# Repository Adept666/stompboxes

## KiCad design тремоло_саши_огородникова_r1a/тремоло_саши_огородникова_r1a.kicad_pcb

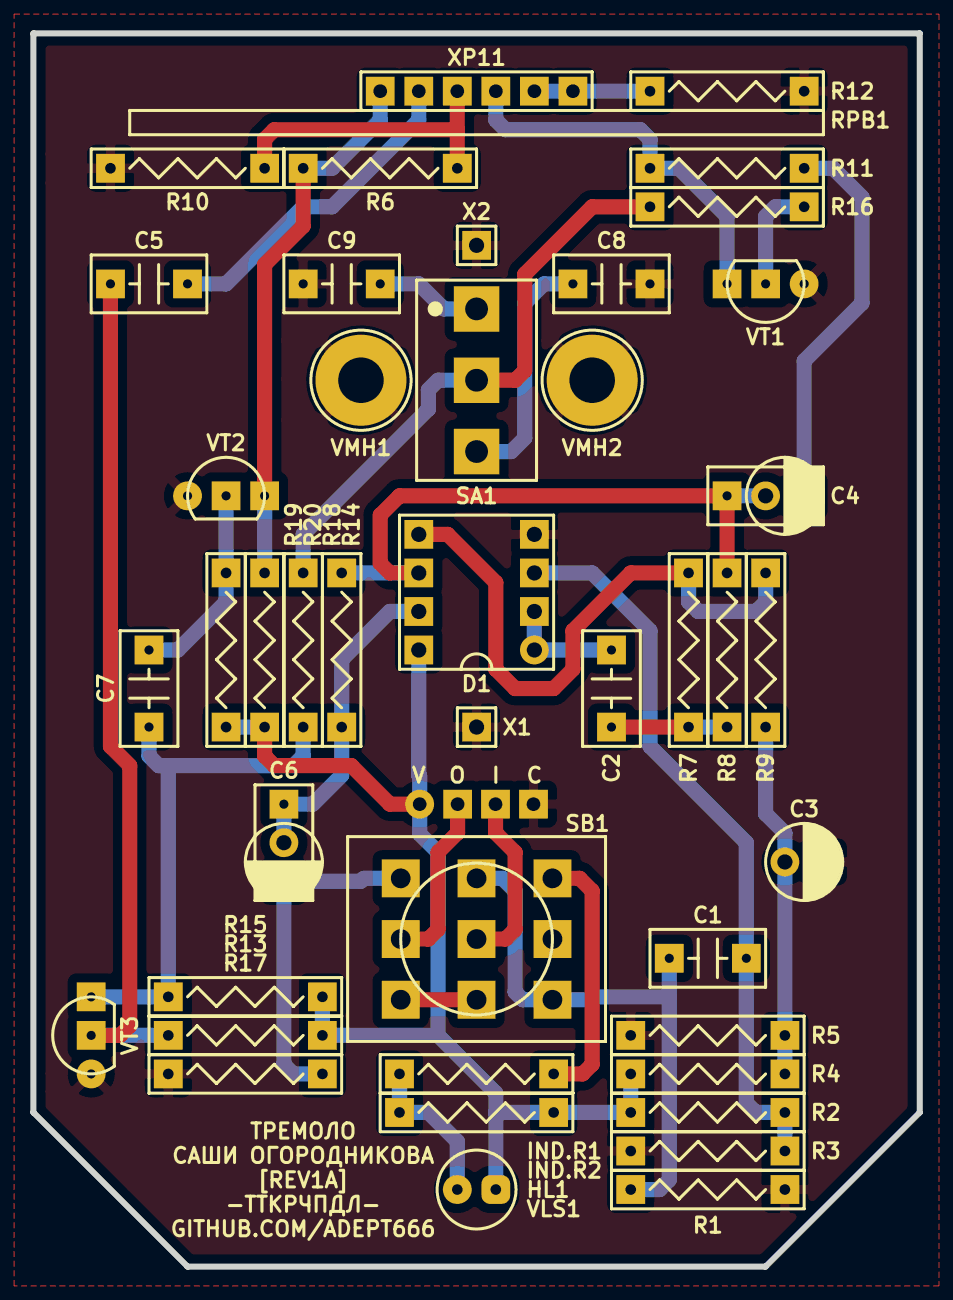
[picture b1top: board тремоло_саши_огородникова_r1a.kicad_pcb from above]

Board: 2 copper layers, 58.4 x 81.3 mm, 47 parts (1 on the bottom side), 29 nets.

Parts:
C1, C2: 104; C-DISK-D04.2-T03.0-P05.08-d0.5
C3: 226; CP-RADIAL-D05.0-P02.0-CLS
C4: 475; C-DISK-D04.2-T03.0-P05.08-d0.5-OR-CP-RADIAL-D05.0-P02.0-CLS
C5, C7: 474; C-DISK-D04.2-T03.0-P05.08-d0.5
C6: 105; C-DISK-D04.2-T03.0-P05.08-d0.5-OR-CP-RADIAL-D05.0-P02.0-CLS
C8: 224; C-DISK-D04.2-T03.0-P05.08-d0.5
C9: 223; C-DISK-D04.2-T03.0-P05.08-d0.5
D1: 4558; P-DIP-08
HL1: FYL-5013URC; LED-ROUND-05.0-UNI-SH-SPACER-PNL-5.3
IND.R1: 472; R-MFR-25
IND.R2: X; R-MFR-25
R1, R13: 225; R-MFR-25
R2, R3: 105; R-MFR-25
R4: 273; R-MFR-25
R5, R8: 303; R-MFR-25
R6: 683; R-MFR-25
R7, R15, R17, R20: 473; R-MFR-25
R9: 393; R-MFR-25
R10: 112; R-MFR-25
R11, R12: 103; R-MFR-25
R14: 333; R-MFR-25
R16, R18: 204; R-MFR-25
R19: 334; R-MFR-25
RPB1: A100K-A100K; RPB-1590N1-18-2x17-1.6-PNL-7.4-2.8
SA1: MTS-102-A2; SW-MTS-102-A2-3.0-PNL-6.0
SB1: PBS-24-302SP; SW-PBS-24-302SP-2.5-PNL-13.0
VE1: 1590N1; 1590N1_A1
VLS1: BR-12.7; VLS-BR
VMH1, VMH2: DI5M3x18; VMH-STA-DA5-PNL-3.0
VT1, VT2, VT3: 5088; P-TO-92-E-B-C
X1, X2: COM; CON-PAD-S-1.0-1.9
XB1: 1590N1 Connector Board; XB-1590N1
XP1: B4B-XH-A; CON-XH-B4B-A

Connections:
/IN-CIR: C1.1, R1.2, SB1.NC3, SB1.NO2
/IN-CON: SB1.COM2, XP1.3
/LED: IND.R1.1, SB1.NO3
/OUT-CIR: C6.-, R17.2, SB1.NO1
/OUT-CON: SB1.COM1, XP1.2
COM: C3.-, C8.2, C9.2, D1.4, R1.1, R3.1, R5.1, R10.1, R12.1, R17.1, SB1.COM3, VMH1.0, VMH2.0, VT1.E, VT2.E, VT3.E, X1.1, X2.1, XP1.4
unnamed: C1.2, D1.3, R2.1, R3.2
unnamed: C2.1, D1.1, D1.2
unnamed: C2.2, R7.1, R8.1
unnamed: C3.+, R4.1, R5.2, R9.1
unnamed: C4.+, D1.6, R8.2, R14.1
unnamed: C4.-, R11.2
unnamed: C5.1, RPB1.12
unnamed: C5.2, R13.1, VT3.B
unnamed: C6.+, D1.7, R14.2
unnamed: C7.1, R15.1, R18.1, VT3.C
unnamed: C7.2, R19.1, VT2.B
unnamed: C8.1, SA1.NO
unnamed: C9.1, SA1.NC
unnamed: D1.5, R7.2, R9.2
unnamed: HL1.C, IND.R1.2, IND.R2.1
unnamed: R6.1, R10.2, RPB1.11
unnamed: R11.1, RPB1.23, VT1.C
unnamed: R12.2, RPB1.21, RPB1.22
unnamed: R16.1, VT1.B
unnamed: R16.2, R18.2, SA1.COM
unnamed: R6.2, R20.1, RPB1.13, VT2.C
unnamed: SB1.NC1, SB1.NC2
V: D1.8, HL1.A, IND.R2.2, R2.2, R4.2, R13.2, R15.2, R19.2, R20.2, XP1.1

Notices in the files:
тремоло_саши_огородникова_r1a/тремоло_саши_огородникова_r1a.kicad_pcb:
This project is licensed under GNU General Public License v3.0 or later
